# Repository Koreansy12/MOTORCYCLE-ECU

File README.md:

# 🚀 FCU32 – Fuel Control Unit Based on ESP32

## 📌 Overview  
**FCU32** is an **experimental project** to build a simple **Fuel Control Unit (ECU)** using the **ESP32** platform.  
The main goal is to control a fuel injector based on standard engine sensors (RPM, MAP, TPS, O2, etc.).  

⚠️ **Disclaimer:**  
This project is still **theoretical**. The components and system have been designed and validated on paper, but **not yet fully realized in hardware**. It’s more like a **concept validation** and research documentation.

---

## 🛠️ Main Components
- **ESP32-S3** (main MCU)  
- **MAP + IAT + TPS Sensor** (from MAQS injector system)  
- **O2 Sensor** (Beat FI)  
- **RPM Pickup Sensor**  
- **Injector (Mio J)**  
- **Power Supply & MOSFET Driver** for injector control  

---

## 📊 Planned Features
- Fuel Injection Control via **lookup/VE table**  
- RPM sensing using **interrupts**  
- TPS & MAP input for engine load calculation  
- O2 sensor input for **closed-loop fuel correction** (planned)  
- UART/I2C communication with a **second ESP32-S3** (for display, logging, fuzzy logic)  
- Multitasking support using **FreeRTOS**  

---

## 📂 Project Status
- ✅ RPM sensor tested on ESP32 (MicroPython)  
- ✅ Pinout and main components planned  
- 🟡 Fuel mapping table (draft stage)  
- 🟡 Injector MOSFET driver (design stage)  
- ❌ Full hardware implementation not yet realized  

---

## 🚧 Next Steps
1. Implement fuel mapping → injector duty cycle control  
2. Test MOSFET driver with actual injector  
3. Integrate O2 sensor for closed-loop correction  
4. Optimize multitasking using FreeRTOS  

---

## ⚡ Why FCU32?
Most aftermarket ECUs are:  
- Expensive 💸  
- Closed-source 🔒  
- Not flexible for DIY/research purposes  

FCU32 aims to be **open-source, affordable, and flexible**, making it suitable for electronics/automotive students and hobbyists who want to experiment.

---

## 📜 License
MIT License – free to use, modify, and develop.  
⚠️ **Note:** This is **not a plug-and-play ECU**. Use at your own risk.

---

## 🤝 Contribution
Contributions are welcome! You can help by:  
- Adding MicroPython / C++ code for injector control  
- Designing hardware (driver + protection circuits)  
- Engine simulation (EngineSim, MATLAB, etc.)  
- Testing on real engines (⚠️ do it at your own risk)  

---

## 🔥 Notes
> This component is theoretically right but has not been realized yet.  
> FCU32 is still in the **concept stage**, and this documentation is mainly to track progress and guide future development.

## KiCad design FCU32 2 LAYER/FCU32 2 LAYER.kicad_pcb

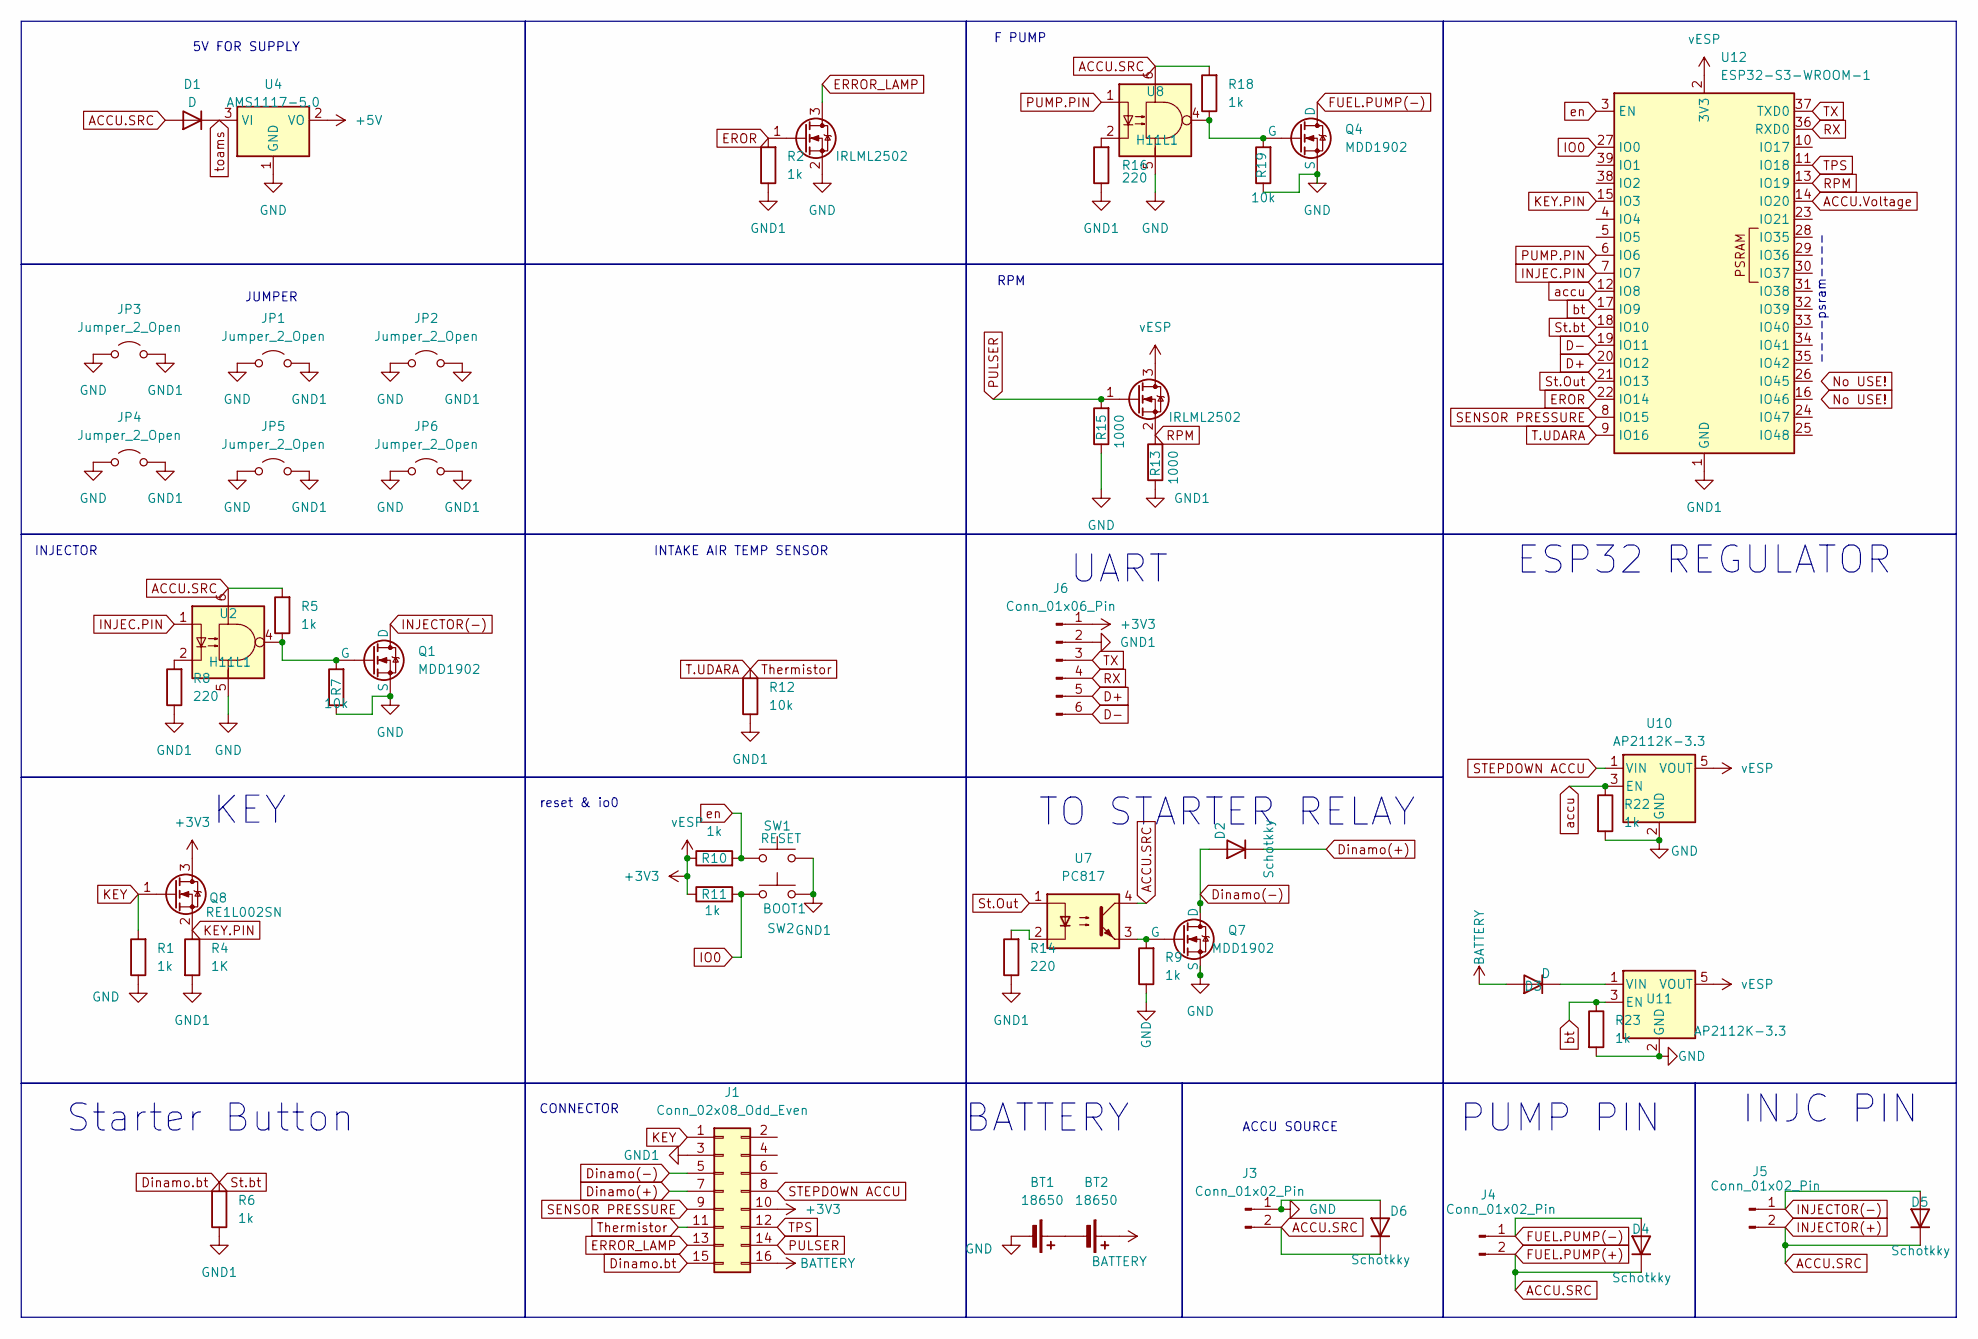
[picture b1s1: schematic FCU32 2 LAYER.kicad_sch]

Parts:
BT1, BT2: 18650
D1, D3: D; D_SMA
D2, D4, D5, D6: Schotkky; D_SMA
J1: Conn_02x08_Odd_Even; PinHeader_2x08_P2.54mm_Horizontal
J3, J4, J5: Conn_01x02_Pin; AMASS_XT30PW-M_1x02_P2.50mm_Horizontal
J6: Conn_01x06_Pin; PinHeader_1x06_P2.54mm_Horizontal
JP1, JP2, JP3, JP4, JP5, JP6: Jumper_2_Open; SolderJumper-2_P1.3mm_Open_RoundedPad1.0x1.5mm
Q1, Q4, Q7: MDD1902; TO-252-2
Q3, Q5: IRLML2502; SOT-23
Q8: RE1L002SN; SOT-416
R1, R2, R5, R6, R9, R10, R11, R18, R22, R23: 1k; R_1206_3216Metric_Pad1.30x1.75mm_HandSolder
R4: 1K; R_1206_3216Metric_Pad1.30x1.75mm_HandSolder
R7, R12, R19: 10k; R_1206_3216Metric_Pad1.30x1.75mm_HandSolder
R8, R14, R16: 220; R_1206_3216Metric_Pad1.30x1.75mm_HandSolder
R13, R15: 1000; R_1206_3216Metric_Pad1.30x1.75mm_HandSolder
SW1: RESET; SW_PUSH_6mm_H4.3mm
SW2: BOOT1; SW_PUSH_6mm_H4.3mm
U2, U8: H11L1; DIP-6_W7.62mm
U4: AMS1117-5.0; SOT-223-3_TabPin2
U7: PC817; DIP-4_W7.62mm
U10, U11: AP2112K-3.3; SOT-23-5
U12: ESP32-S3-WROOM-1

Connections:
+3V3: J1.10, J6.1, Q5.3 (D), Q8.3 (D), R10.1, R11.1, U10.5 (VOUT), U11.5 (VOUT), U12.2 (3V3)
+5V: U4.2 (VO)
ACCU.SRC: D1.2 (A), D4.1 (K), D5.1 (K), D6.1 (K), J3.2, J4.2, J5.2, R5.2, R18.2, U2.6, U7.4, U8.6
ACCU.Voltage: U12.14 (IO20)
BATTERY: BT2.1 (+), D3.2 (A), J1.16
D+: J6.5, U12.20 (IO12)
D-: J6.6, U12.19 (IO11)
Dinamo(+): D2.1 (K), J1.7
Dinamo(-): D2.2 (A), J1.5, Q7.1 (D)
Dinamo.bt: J1.15, R6.2, U12.18 (IO10)
EROR: Q3.1 (G), R2.2, U12.22 (IO14)
ERROR_LAMP: J1.13, Q3.3 (D)
FUEL.PUMP(-): D4.2 (A), J4.1, Q4.1 (D)
GND: BT1.2 (-), D6.2 (A), J3.1, JP1.1 (A), JP2.1 (A), JP3.1 (A), JP4.1 (A), JP5.1 (A), JP6.1 (A), Q1.3 (S), Q3.2 (S), Q4.3 (S), Q7.3 (S), R1.1, R7.1, R9.1, R15.1, R19.1, R22.2, R23.2, U2.5, U4.1 (GND), U8.5, U10.2 (GND), U11.2 (GND)
GND1: J1.3, J6.2, JP1.2 (B), JP2.2 (B), JP3.2 (B), JP4.2 (B), JP5.2 (B), JP6.2 (B), R2.1, R4.2, R6.1, R8.1, R12.1, R13.1, R14.1, R16.1, SW1.2, SW2.2, U12.1 (GND), U12.40 (GND), U12.41 (GND)
INJEC.PIN: U2.1, U12.7 (IO7)
INJECTOR(-): D5.2 (A), J5.1, Q1.1 (D)
IO0: R11.2, SW2.1, U12.27 (IO0)
KEY: J1.1, Q8.1 (G), R1.2
KEY.PIN: Q8.2 (S), R4.1, U12.15 (IO3)
unnamed: BT1.1 (+), BT2.2 (-)
unnamed: D3.1 (K), U11.1 (VIN)
unnamed: Q1.2 (G), R5.1, R7.2, U2.4
unnamed: Q4.2 (G), R18.1, R19.2, U8.4
unnamed: Q7.2 (G), R9.2, U7.3
unnamed: R8.2, U2.2
unnamed: R14.2, U7.2
unnamed: R16.2, U8.2
PULSER: J1.14, Q5.1 (G), R15.2
PUMP.PIN: U8.1, U12.6 (IO6)
RPM: Q5.2 (S), R13.2, U12.13 (IO19)
RX: J6.4, U12.36 (RXD0)
SENSOR PRESSURE: J1.9, U12.8 (IO15)
STEPDOWN ACCU: J1.8, U10.1 (VIN)
St.Out: U7.1, U12.21 (IO13)
T.UDARA: J1.11, R12.2, U12.9 (IO16)
TPS: J1.12, U12.11 (IO18)
TX: J6.3, U12.37 (TXD0)
accu: R22.1, U10.3 (EN), U12.12 (IO8)
bt: R23.1, U11.3 (EN), U12.17 (IO9)
en: R10.2, SW1.1, U12.3 (EN)
toams: D1.1 (K), U4.3 (VI)

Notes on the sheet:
PUMP PIN
reset & io0
BATTERY
UART
F PUMP
ACCU SOURCE
----psram----
INJC PIN
TO STARTER RELAY
RPM
JUMPER
5V FOR SUPPLY
INTAKE AIR TEMP SENSOR
CONNECTOR
INJECTOR
Starter Button
ESP32 REGULATOR
KEY

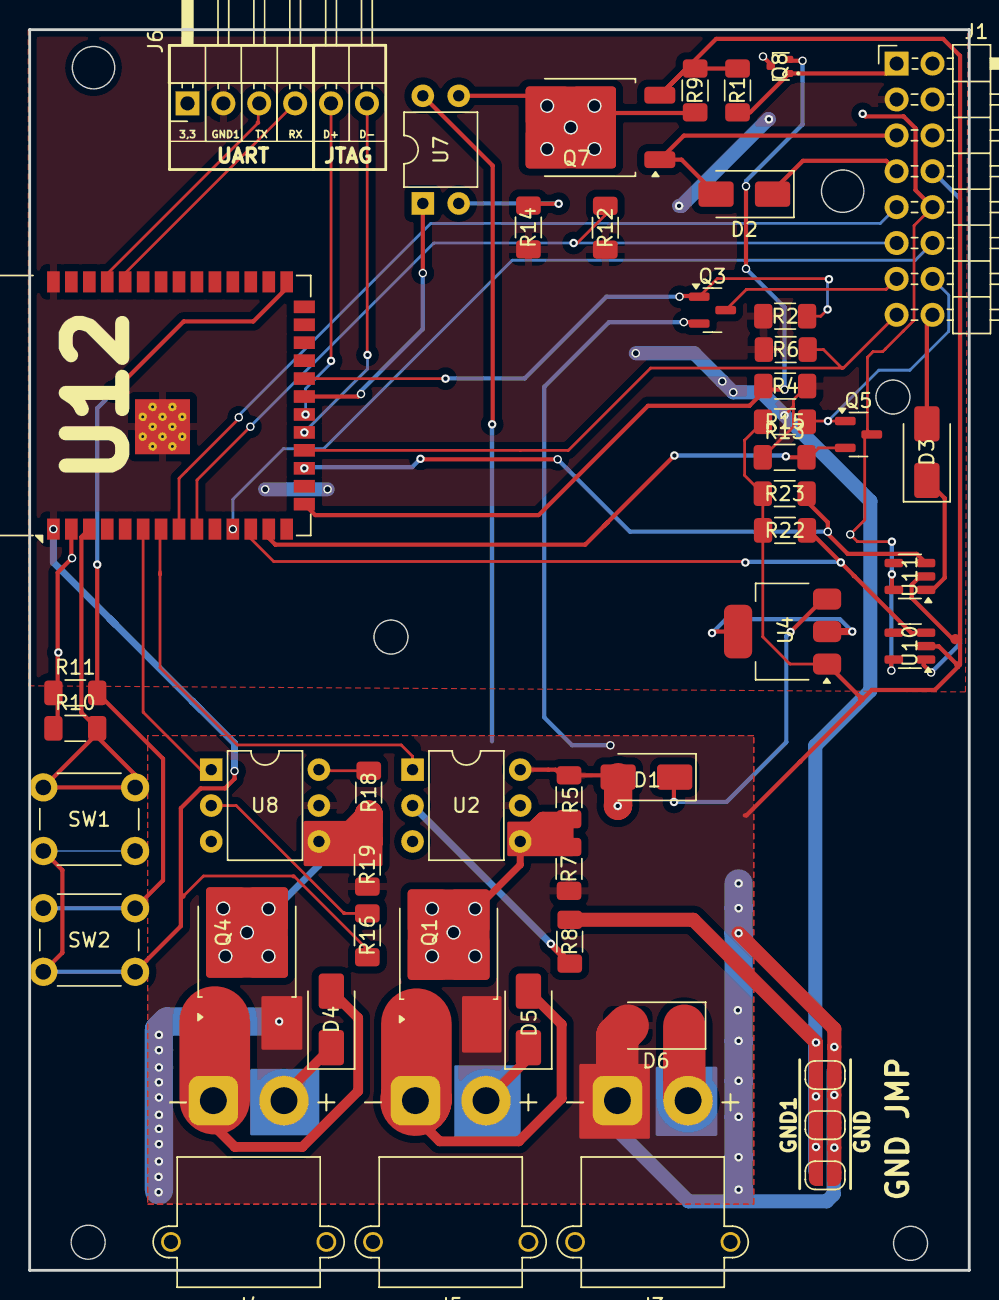
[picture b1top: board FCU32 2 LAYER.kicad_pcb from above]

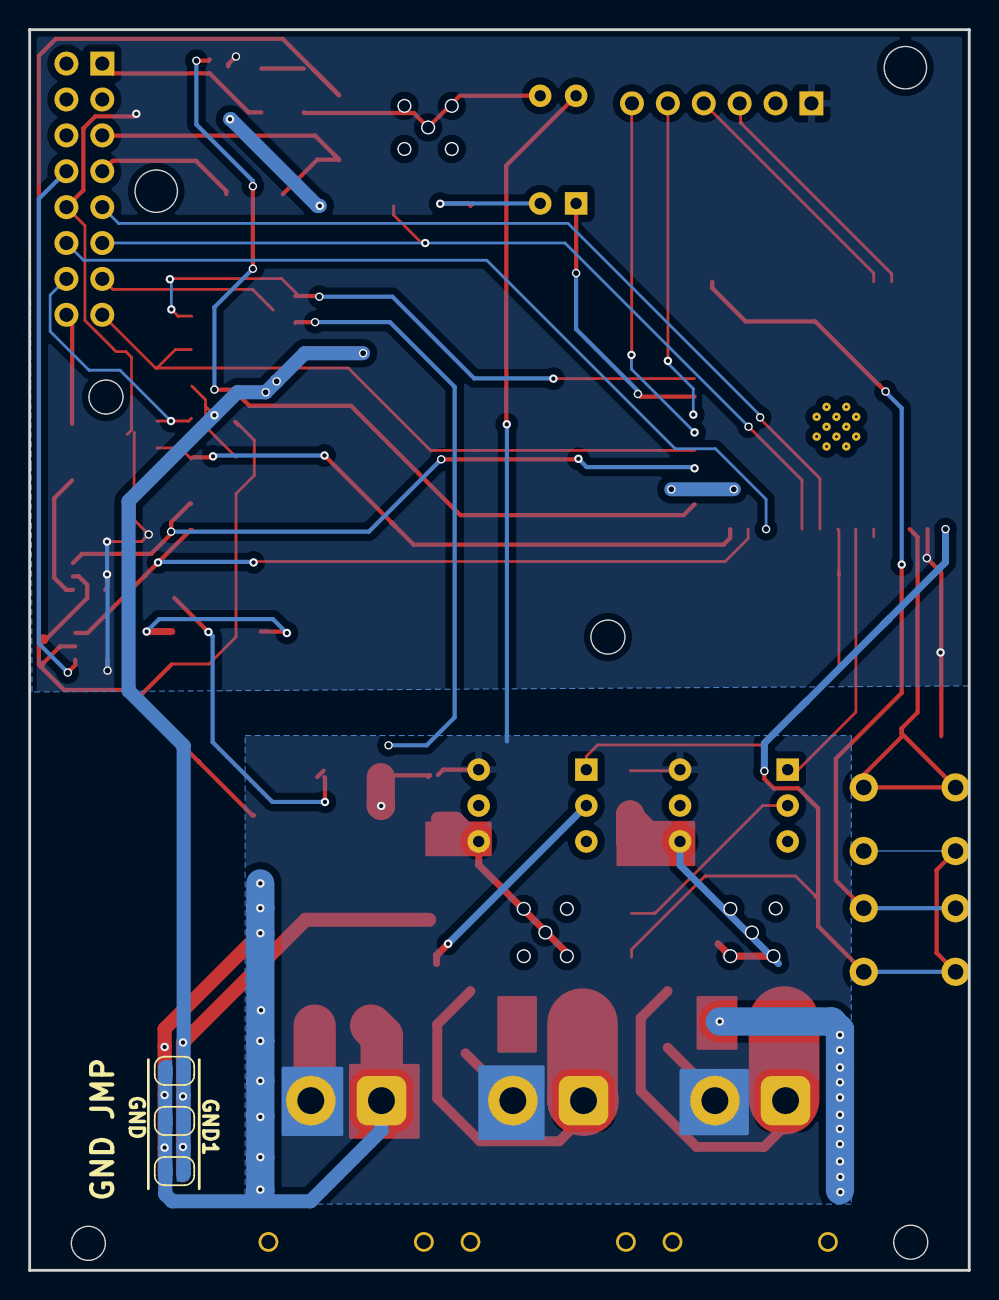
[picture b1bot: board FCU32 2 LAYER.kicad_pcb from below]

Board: 2 copper layers, 66.5 x 87.8 mm, 51 parts (3 on the bottom side), 39 nets.

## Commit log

2025-08-21 Create FCU32 2 LAYER PCB
